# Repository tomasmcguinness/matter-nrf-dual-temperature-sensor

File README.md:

# Nordic nRF Matter Dual Temperature Sensor

This is my Matter Dual Temperature Sensor, powered by the Nordic Semiconductors nRF54L15.

## Probes

- Supports two NTC thermistor probes connected via 2-pin JST-PH connectors.
- Allowing for two temperature readings.
- It uses the standard Temperature Measurement cluster, presented on two endpoints, representing Probe 1 and Probe 2.

> [!CAUTION]
> This is designed to work as an ICD (Intermittent Connected Device), so any controller that commissions it must support the ICD mechanism.

## Battery Life

The firmware has been optimised to reduce power consumption using Matter ICD (Intermittant Connected Device) and LIT (Long Idle Time)

It consumes an average 18µA, which allows for approximately 1.5 years on a standard 240mAh 2032 coin cell battery. 

The cell voltage is reported through the standard Matter PowerSource cluster, so the remaining battery level shows up in the controller alongside the two temperatures. The coin cell drives VDD directly, so the level is read from the SAADC's internal VDD input and costs no extra hardware.

## Firmware

The code is written using the Nordic Connect SDK, v3.3.0.

### TODO

- [x] Implement ADC
- [x] Add two temperature probes
- [x] Basic indicator LED (without DK)
- [x] Press and hold to reset
- [x] User labels to name the probes
- [x] Report the battery level
- [x] Custom cluster reporting both probes from one endpoint

## Hardware

There is a PCB design, which you'll find under the firmware folder.

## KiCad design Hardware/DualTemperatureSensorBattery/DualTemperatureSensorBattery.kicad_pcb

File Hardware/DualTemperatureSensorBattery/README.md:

# Bill of Materials (BOM)

This page is just a scratch pad as I try to figure out the bill of materials.

LDO
MCP1700T-2202E/TT

Push Button
TS04-66-48-BK-100-SMT

Connectors
S2B-PH-SM4-TB

LED
HSMH-H170

Capacitors
C0805Y104K1RACAUTO

Resistors
AR0805FR-07330RL
RNCE0805BTE10K0

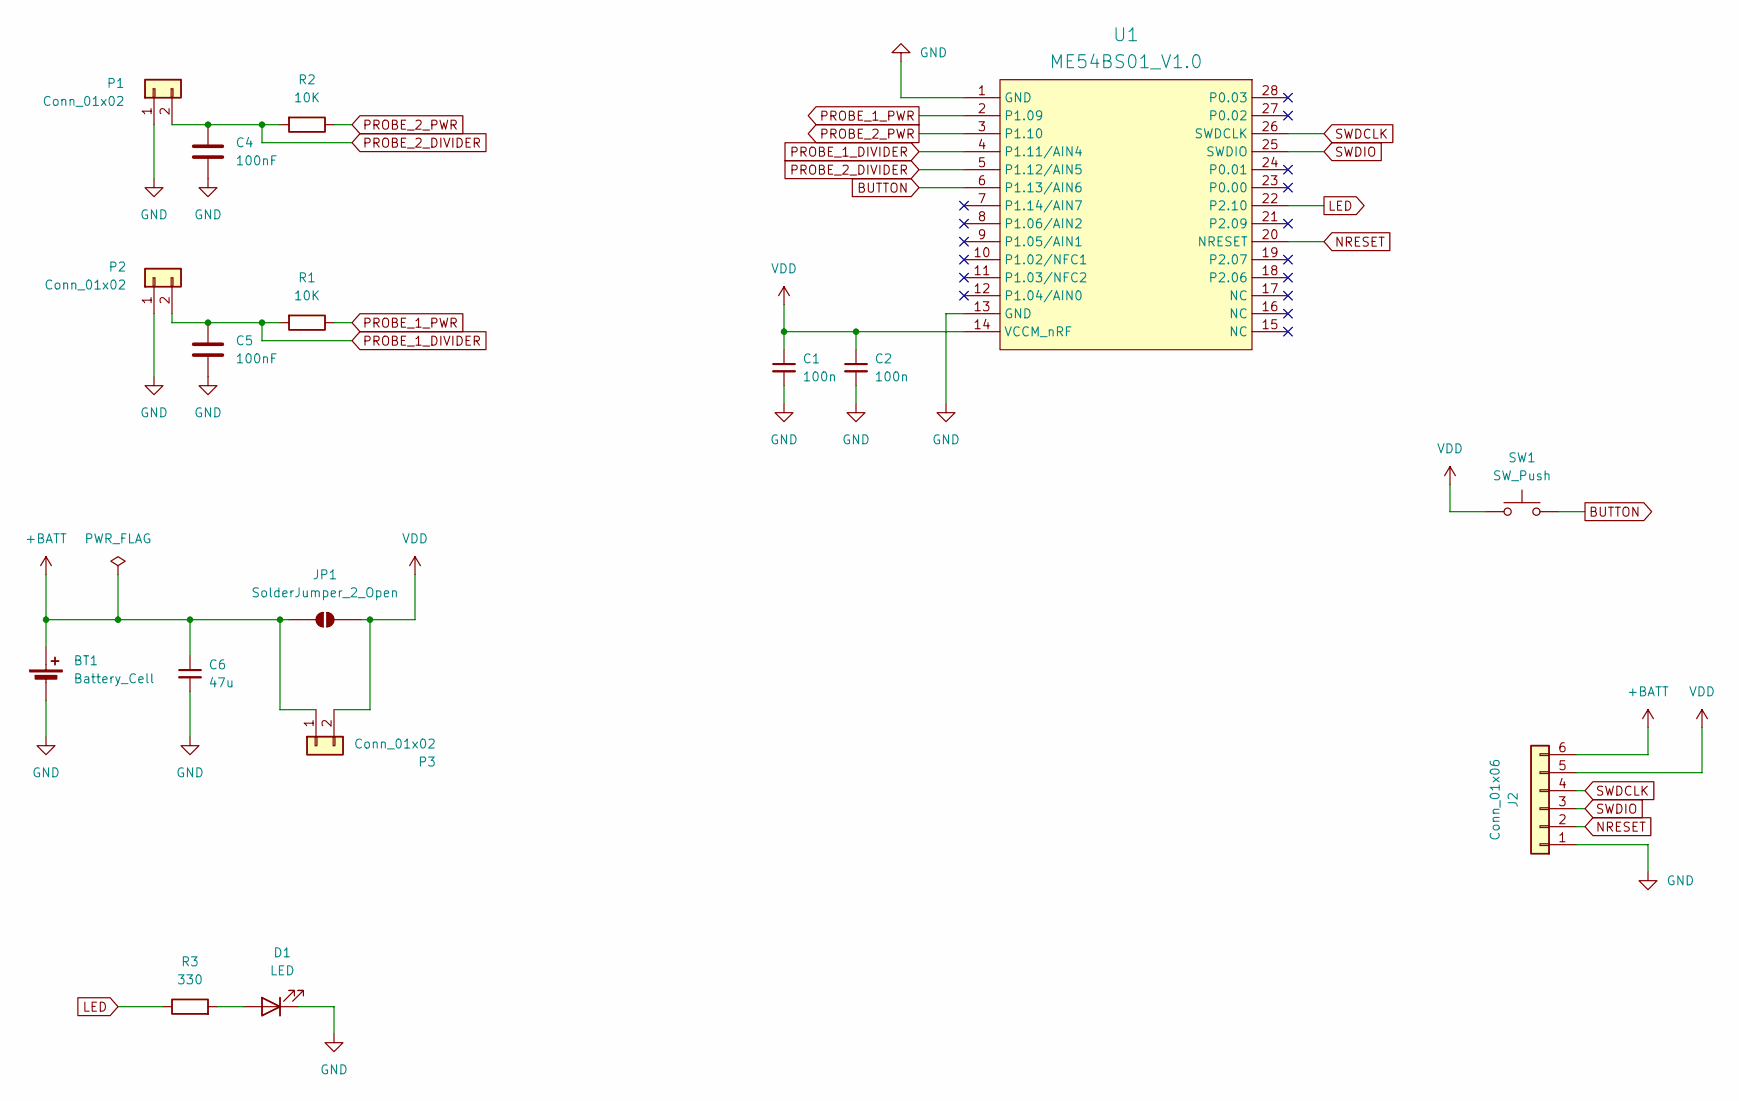
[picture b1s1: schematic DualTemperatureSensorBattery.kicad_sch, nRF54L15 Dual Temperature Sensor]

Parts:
BT1: Battery_Cell; BatteryHolder_Keystone_3034_1x20mm
C1, C2: 100n; C_0805_2012Metric; mouser# 581-04025C104KAT4A
C4, C5: 100nF; C_0805_2012Metric
C6: 47u; C_0805_2012Metric; mouser# 581-04025C104KAT4A
D1: LED; LED_0805_2012Metric
J2: Conn_01x06; PinHeader_1x06_P2.54mm_Vertical
JP1: SolderJumper_2_Open; SolderJumper-2_P1.3mm_Open_RoundedPad1.0x1.5mm
P1, P2: Conn_01x02; JST_PH_B2B-PH-SM4-TB_1x02-1MP_P2.00mm_Vertical
P3: Conn_01x02; PinSocket_2x01_P2.54mm_Vertical
R1: 10K; R_0805_2012Metric
R2: 10K; R_0805_2012Metric_Pad1.20x1.40mm_HandSolder
R3: 330; R_0805_2012Metric
SW1: SW_Push; SW_SPST_TS-1088-xR025
U1: ME54BS01_V1.0

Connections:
+BATT: BT1.1 (+), C6.1, J2.6, JP1.1 (A), P3.1
BUTTON: SW1.2, U1.6 (P1.13/AIN6)
GND: BT1.2 (-), C1.2, C2.2, C4.2, C5.2, C6.2, D1.1 (K), J2.1, P1.1, P2.1, U1.1 (GND), U1.13 (GND)
LED: R3.1, U1.22 (P2.10)
NRESET: J2.2, U1.20 (NRESET)
unnamed: D1.2 (A), R3.2
PROBE_1_DIVIDER: C5.1, P2.2, R1.2, U1.4 (P1.11/AIN4)
PROBE_1_PWR: R1.1, U1.2 (P1.09)
PROBE_2_DIVIDER: C4.1, P1.2, R2.2, U1.5 (P1.12/AIN5)
PROBE_2_PWR: R2.1, U1.3 (P1.10)
SWDCLK: J2.4, U1.26 (SWDCLK)
SWDIO: J2.3, U1.25 (SWDIO)
VDD: C1.1, C2.1, J2.5, JP1.2 (B), P3.2, SW1.1, U1.14 (VCCM_nRF)

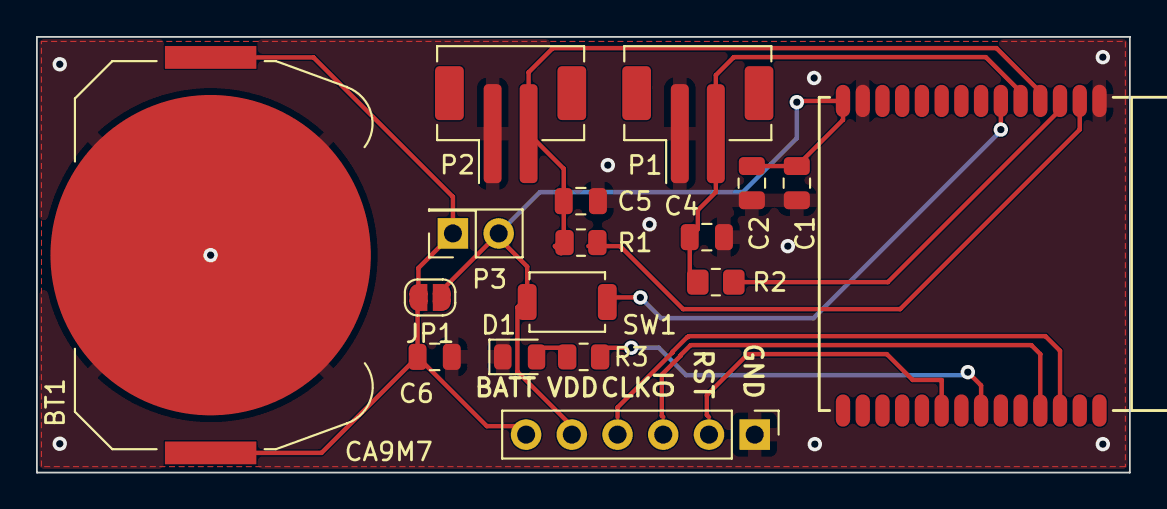
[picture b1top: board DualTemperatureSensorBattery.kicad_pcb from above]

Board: 2 copper layers, 60.7 x 24.2 mm, 17 parts (0 on the bottom side), 13 nets.

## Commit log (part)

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2025-07-08 Initial checkin
2025-07-08 Rename README.rst to README.md
2025-07-09 Add two temperature measurement clusters
2025-07-09 Ported the basic code over. Removed lots of unused files. Probe 1 is working. Probe 2 is untested.
2025-07-14 Power consumption with sensors off is not at 70µA
2025-07-14 Remove commented code. Set slow poll to 30 seconds.
2025-07-16 Remove on/off cluster. Further tweaks to try and get power consumption down.
2025-07-18 Restore code that reads temperature via ADC
2025-08-08 Restore basic template sample
2025-08-08 Add two temperature sensor endpoints, updating with random value every 5 seconds.
2025-08-09 Disable qspi and spi2 peripherals in the DK overlay
2025-08-09 Add ICD settings to the configuration
2025-08-09 Add ICD settings
2025-08-09 Remove the unused overlays and partitions
2025-08-11 Enable ACD
2025-08-13 Ignore named build folder
2025-08-13 Add divider power pin support
2025-08-13 Remove old README.rst file
2025-08-29 Add a second divider power output to improve accuracy
2025-09-01 Add overlay and partition file for nRF54L15
2025-09-01 Add WIP PCB
2025-09-01 Move existing files into Software folder
2025-09-01 Add KiCad lock file to gitignore
2025-09-02 Reset back to Template sample in NCS v3.1.0
2025-09-03 Small tweaks
2025-09-04 Rename Software to Firmware. Make first changes for new Clusters.
2025-09-04 Trying to reduce power consumption
2025-09-10 Switch off the LEDs in config. Restore the board init and callback.
2025-09-10 Enable ADC peripheral. Disable CHIP Shell for size.
2025-09-10 Add ADC reading code and divider power configuration
2025-09-11 Switch GPIO ports for power. Turn off Flash protection. Tweak timer delay.
2025-09-11 Configure GPIOs for power and ADC
2025-09-11 Get ADC reference voltage using API.
2025-09-13 Working on getting ADC channel 0 reading correctly.
2025-09-13 More work to get single ADC channel working
2025-09-16 Restore Matter server to working order.
2025-09-17 Work on PCB
2025-09-19 ADC working on AIN4 & AIN5
2025-09-19 Both power and ADC is working
2025-10-09 Add simple indicator light support. Add overlay for reset button.
2025-10-10 Add empty readme
2025-10-10 Some steps
2025-10-15 Comment out code to try and diagnost boot issue
2025-10-16 Restore the template sample to try and fix the build issue.
2025-10-16 Restore app_task implementation. Updated overlay and project config
2025-10-16 Update template.zap with temperature clusters
2025-10-16 Include sysbuild folder (include the mcu bootloader!)
2025-10-16 Remove template folder (copy/paste mistake I think)
2025-10-17 Change some config for the PCB design
2025-10-17 Update PCB with new pin outs
2025-10-17 Remove Zone.Identifier files
2025-10-18 Update the PCB
2025-10-18 Another small PCB update
2025-10-19 WIP Reworking schematic with Reddit feedback
2025-10-20 Cleaned up schematic to be all in one. Trying to get updated layout for PCB
2025-10-20 Another PCB update
2025-10-22 PCB: Add another PIN to the header so power can be provided via J-Link.
2025-10-24 Move decoupling capacitors closer to LDO. Ground module PIN 1.
2025-10-24 Move decoupling capacitors even closer
2025-10-24 Another backup
2025-10-27 Start of a README for the PCB
2025-11-03 Add debug and K32 config
2025-11-03 Add new minewsemi configuration files.
2025-11-18 Fix Nordic DevKit build. Use DK LED and Button configuration.
2025-11-19 Have restored prj.conf and nrf54l15dk overlay back to working order.
2025-11-19 Implement Identify cluster support
2025-11-19 Power consumption down to 100µA
2025-11-19 Bring power config into the release file. Remove unused nrf54L10 overlay.
2025-11-19 Add device configuration to the internal overlay
2025-11-20 Increase sensor reading to 30 second frequency. Turn off LOG and CONSOLE
2025-11-20 Update PCB with fix for LDO and tracing improvements.
2025-11-21 Fix sensor timer
2025-11-21 Clock settings for MinewSemi
2025-11-25 Small tweak of reference voltage to 2.2V
2025-11-28 Fix Reset button PIN.
2025-11-28 Update readme.
2025-12-02 Update firmware features to completed status
2025-12-08 Revision 2 of the PCB using all SMD components
2025-12-13 Reset is kinda working
2025-12-15 BOM and small tweaks
2025-12-17 Enabled logging in dev. Increased temperture read frequency to 5 seconds.
2025-12-24 Commented out broken logging
2025-12-24 Some read me information
2025-12-24 Remove usuless header
2025-12-24 Add a photo
2025-12-31 Turn LED on for 1 second on boot. Small logging tweaks and code cleanup.
2025-12-31 KiCad Backup change
2025-12-31 Turn on LED when reset button is pressed. Add more logging
2026-01-06 Switch Reset Button from GPIO2 to GPIO1 to fix issue when MCU is asleep.
2026-01-07 Add configuration for both battery and main
2026-01-07 Move some of the cmake files from the samples/common to this project to reduce dependency
2026-01-07 Implemented FixedLabel support
2026-01-07 Update README to mark user labels task as complete
    https://tomasmcguinness.com/2026/01/07/dual-temperature-sensor-configuring-fixedlabels-in-matter/
2026-01-10 new conf files for usb/battery
2026-01-12 Add new clusters for power source
2026-01-12 Change conf files names to better reflect cluster
2026-01-15 Update the readme
2026-01-15 Enable property ICD support in Battery configuration.
2026-01-15 Comment out the OnNetworkActivity() call
2026-01-15 Change conf file naming.
2026-01-15 Created Wired ZAP configuration
2026-02-01 Changes to reduce power consumption. 1-minute average now 18µA
2026-02-03 Enhance README with additional product details
    Expanded the README to include details about temperature probe support, battery life, and firmware version.
2026-02-14 Switch reset interrupt to GPIO_INT_EDGE_TO_ACTIVE. Restore UART for DK overlay. Make wired a Full Thread Device. Tidy up logging configuration. Turn off Thread SSED.
2026-02-15 Update README with work in progress note
    Added a note indicating that the project is a work in progress.
2026-02-15 Update README with progress note and PCB design info
    Clarified the work in progress note and updated PCB design location.
2026-02-16 Starting different PCB designs for USB & Battery
2026-02-18 Config RTT logs. Remove SSED setting. Update readme with correct wired.conf file name.
2026-02-26 Fix TX power to 8. Update SPI config to work with NCS 3.2
2026-02-26 Add ThreadNetworkDiagnosticsCluster
2026-03-16 Remove unused CPUs
2026-03-16 Small tweaks suggested by Claude
